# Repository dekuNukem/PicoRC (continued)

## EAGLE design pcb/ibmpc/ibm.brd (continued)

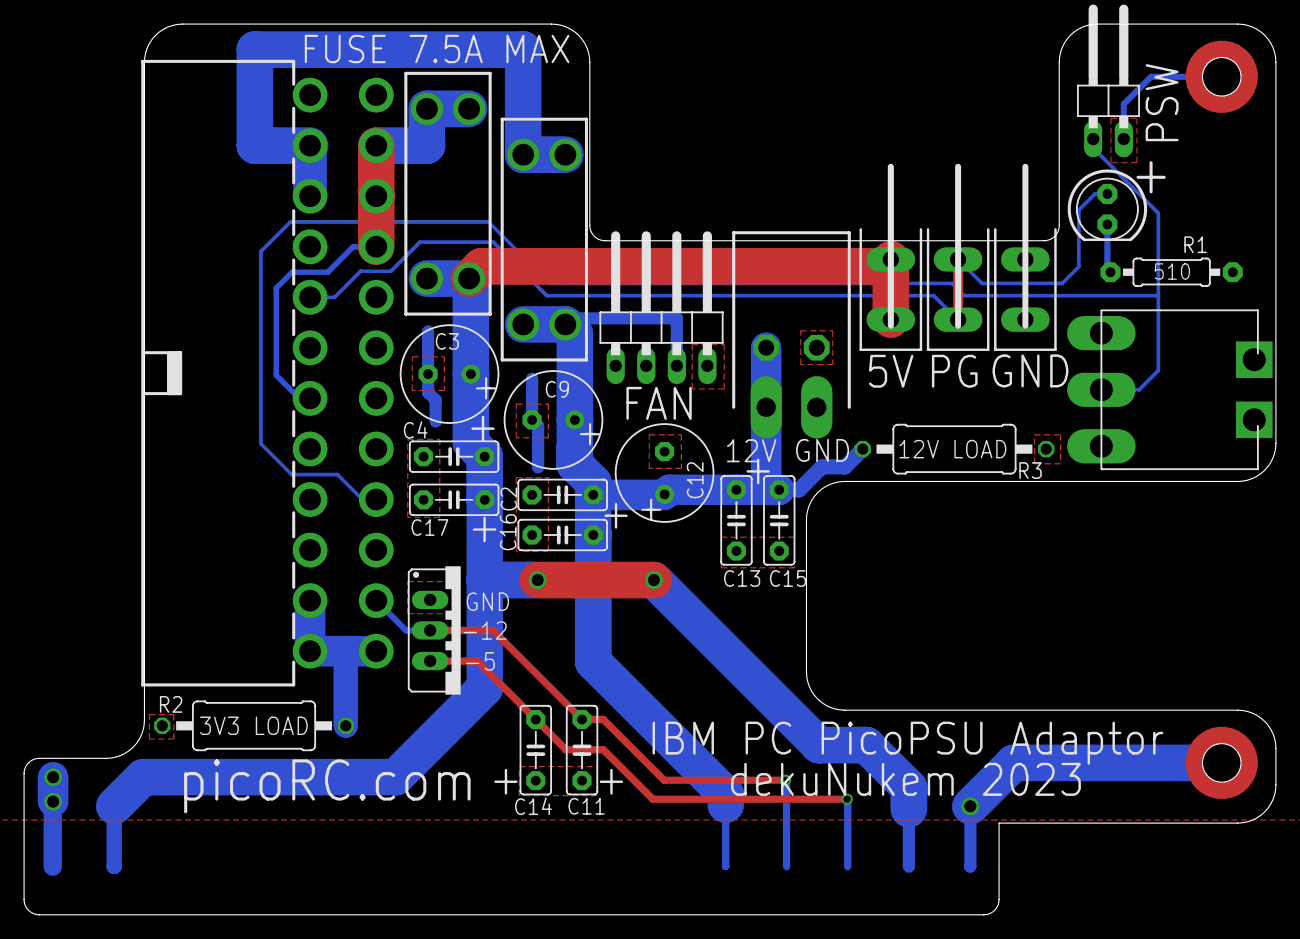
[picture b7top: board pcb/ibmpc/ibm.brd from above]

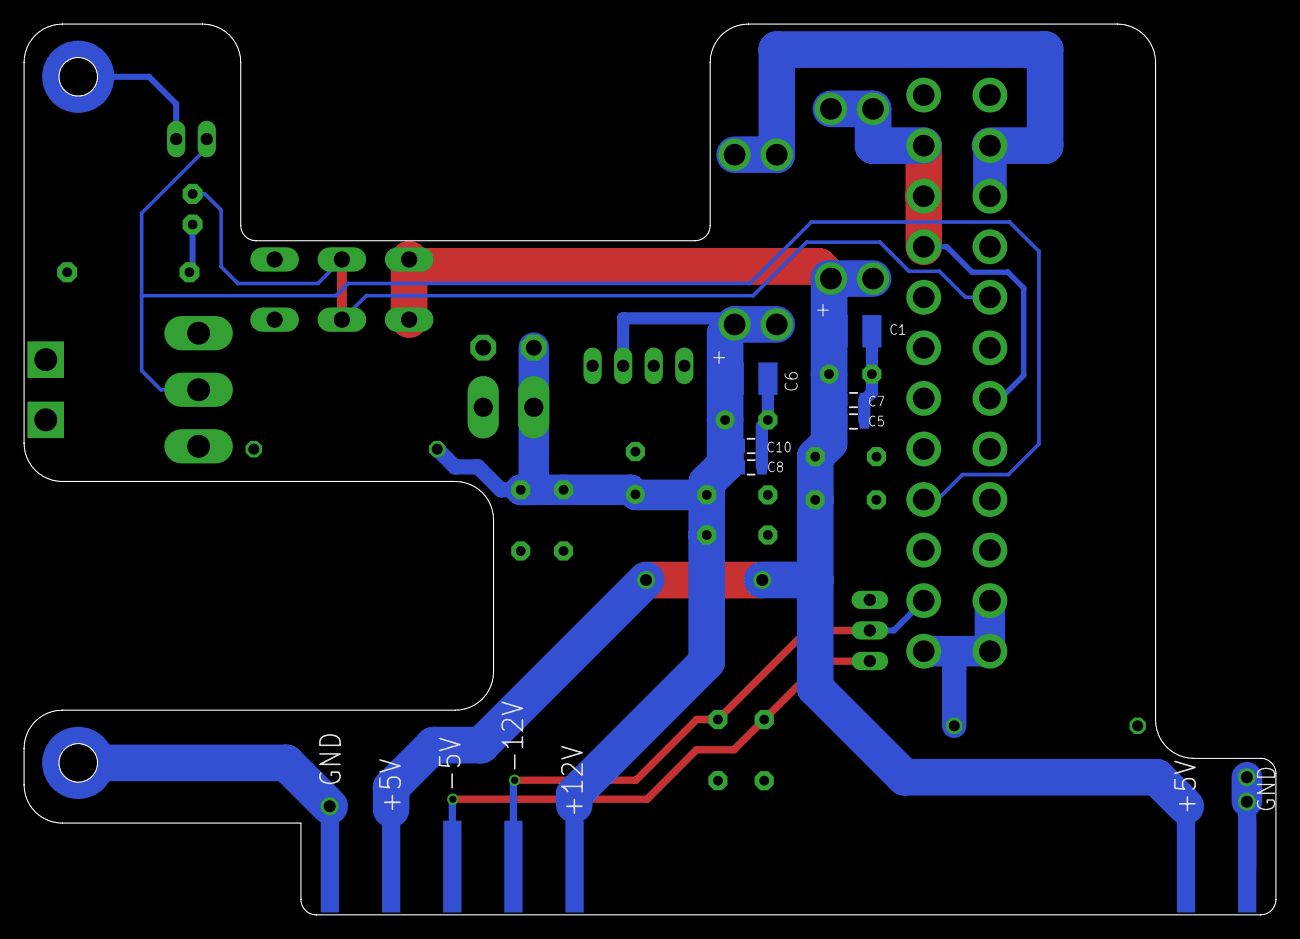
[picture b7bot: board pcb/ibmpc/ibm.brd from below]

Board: 2 copper layers, 104.0 x 74.0 mm, 43 parts (13 on the bottom side), 11 nets.

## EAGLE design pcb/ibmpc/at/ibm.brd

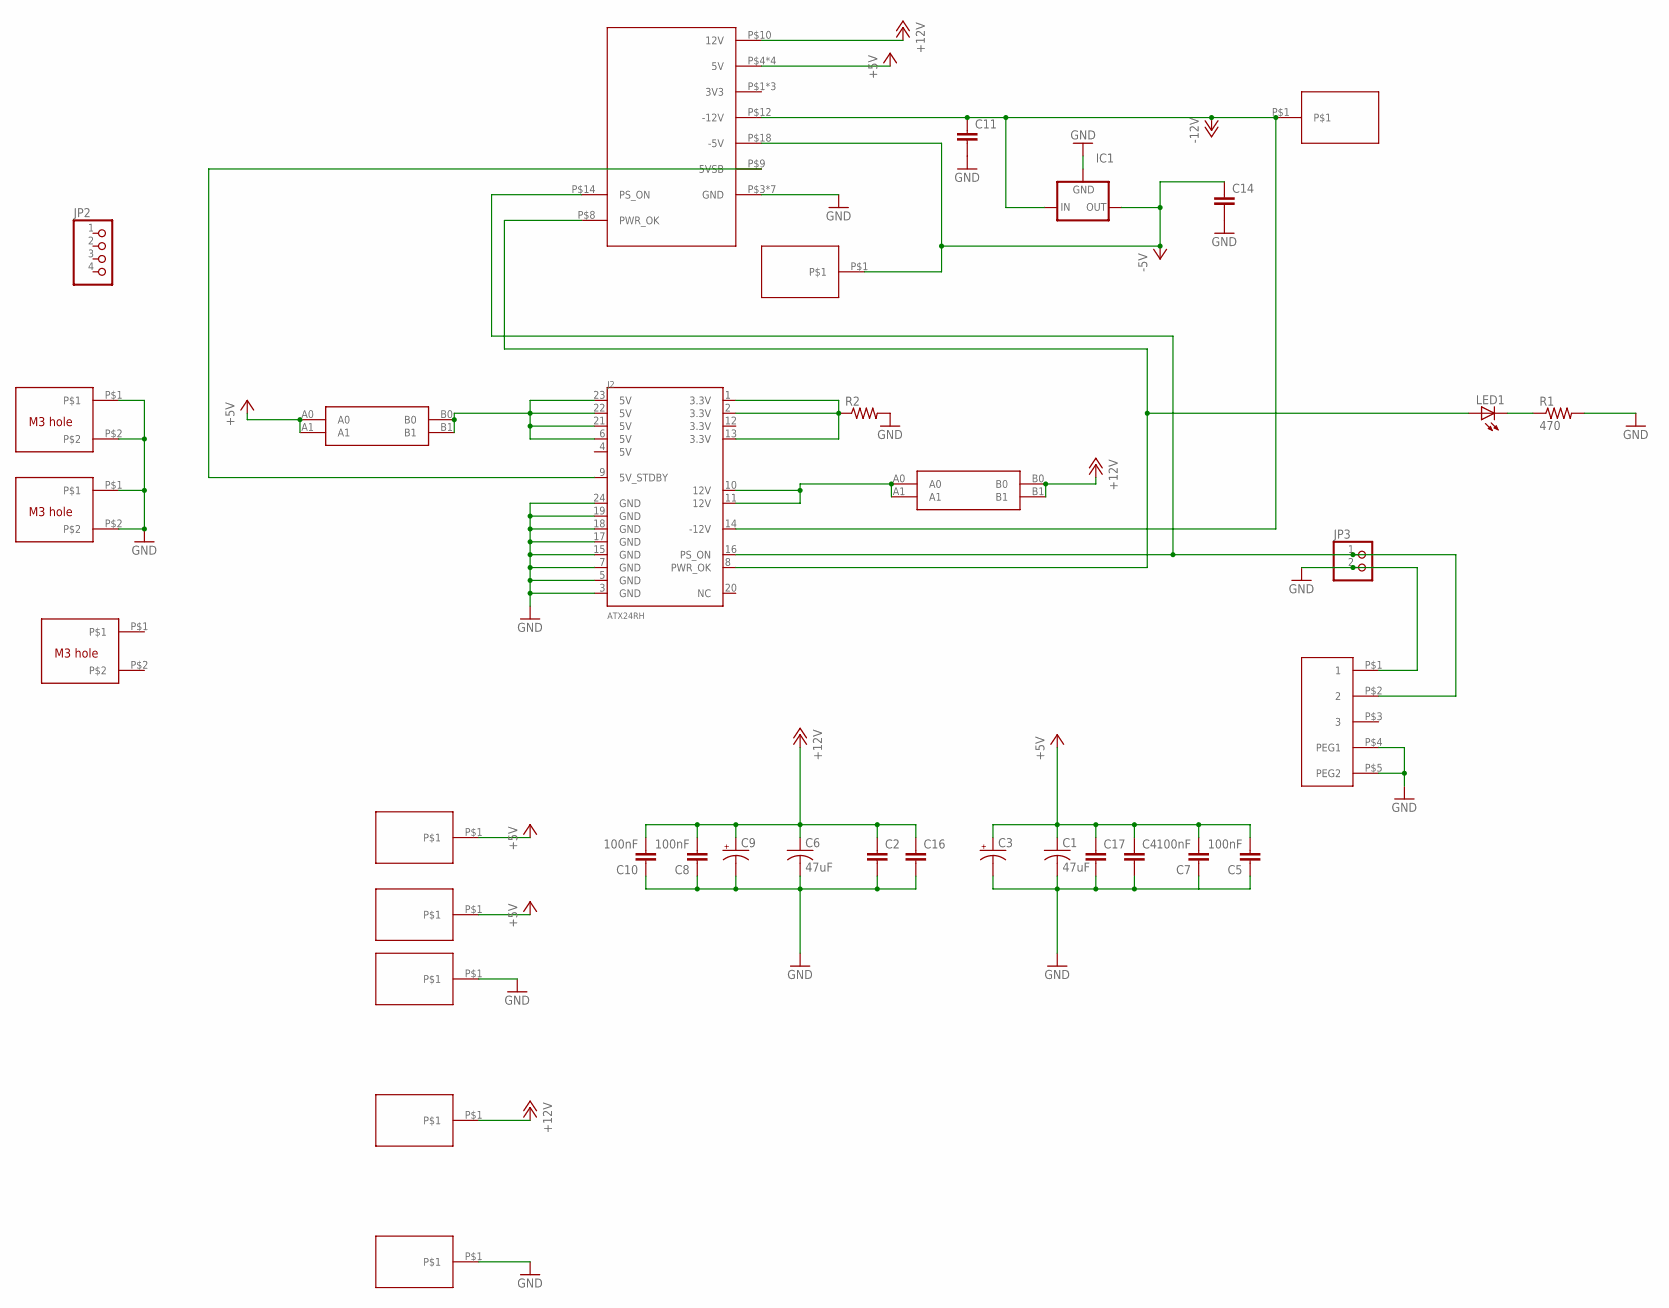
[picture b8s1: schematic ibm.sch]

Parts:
C1, C6: 47uF; C1210
C2, C4, C11, C14, C16, C17: C5/2.5; C5B2.5
C3, C9: CPOL-USE3.5-8; E3,5-8
C5, C7, C8, C10: 100nF; 0805@1
IC1: 79XXS
J2: ATX24RH; ATX24_RIGHT_ANGLE
JP2: PINHD-1X4/90; 1X04/90
JP3: PINHD-1X2/90; 1X02/90
LED1: LED5MM
R1: 470; 0207/10
R2: R-US_0411/15; 0411/15
U$1: 20PEDGE; 20P_EDGE
U$2, U$8: CAR_FUSE_HOLDER3IN1; FUSE_HOLDER_3IN1
U$3, U$7, U$9, U$10, U$13, U$15, U$16: ISA; ISAPAD
U$4: ROCKSW
U$5, U$6, U$11: M3_MOUNTING_HOLE; M3_MOUNTING_HOLE_PACK

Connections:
+5V: C1.1, C3.+, C4.1, C5.2, C7.2, C17.1, U$1.P$4 (5V), U$1.P$6 (5V), U$1.P$19 (5V), U$1.P$20 (5V), U$3.P$1, U$8.A0, U$8.A1, U$16.P$1
+12V: C2.1, C6.1, C8.2, C9.+, C10.2, C16.1, U$1.P$10 (12V), U$2.B0, U$2.B1, U$13.P$1
-5V: C14.1, IC1.OUT, U$1.P$18 (-5V), U$7.P$1
-12V: C11.1, IC1.IN, J2.14 (-12V), U$1.P$12 (-12V), U$10.P$1
GND: C1.2, C2.2, C3.-, C4.2, C5.1, C6.2, C7.1, C8.1, C9.-, C10.1, C11.2, C14.2, C16.2, C17.2, IC1.GND, J2.3 (GND), J2.5 (GND), J2.7 (GND), J2.15 (GND), J2.17 (GND), J2.18 (GND), J2.19 (GND), J2.24 (GND), JP3.2, R1.2, R2.2, U$1.P$3 (GND), U$1.P$5 (GND), U$1.P$7 (GND), U$1.P$13 (GND), U$1.P$15 (GND), U$1.P$16 (GND), U$1.P$17 (GND), U$4.P$1 (1), U$4.P$4 (PEG1), U$4.P$5 (PEG2), U$5.P$1, U$5.P$2, U$6.P$1, U$6.P$2, U$9.P$1, U$15.P$1
unnamed: J2.1 (3.3V), J2.2 (3.3V), J2.13 (3.3V), R2.1
unnamed: J2.16 (PS_ON), JP3.1, U$1.P$14 (PS_ON), U$4.P$2 (2)
unnamed: J2.8 (PWR_OK), LED1.A, U$1.P$8 (PWR_OK)
unnamed: J2.9 (5V_STDBY), U$1.P$9 (5VSB)
unnamed: J2.6 (5V), J2.21 (5V), J2.22 (5V), J2.23 (5V), U$8.B0, U$8.B1
unnamed: J2.10 (12V), J2.11 (12V), U$2.A0, U$2.A1
unnamed: LED1.K (C), R1.1

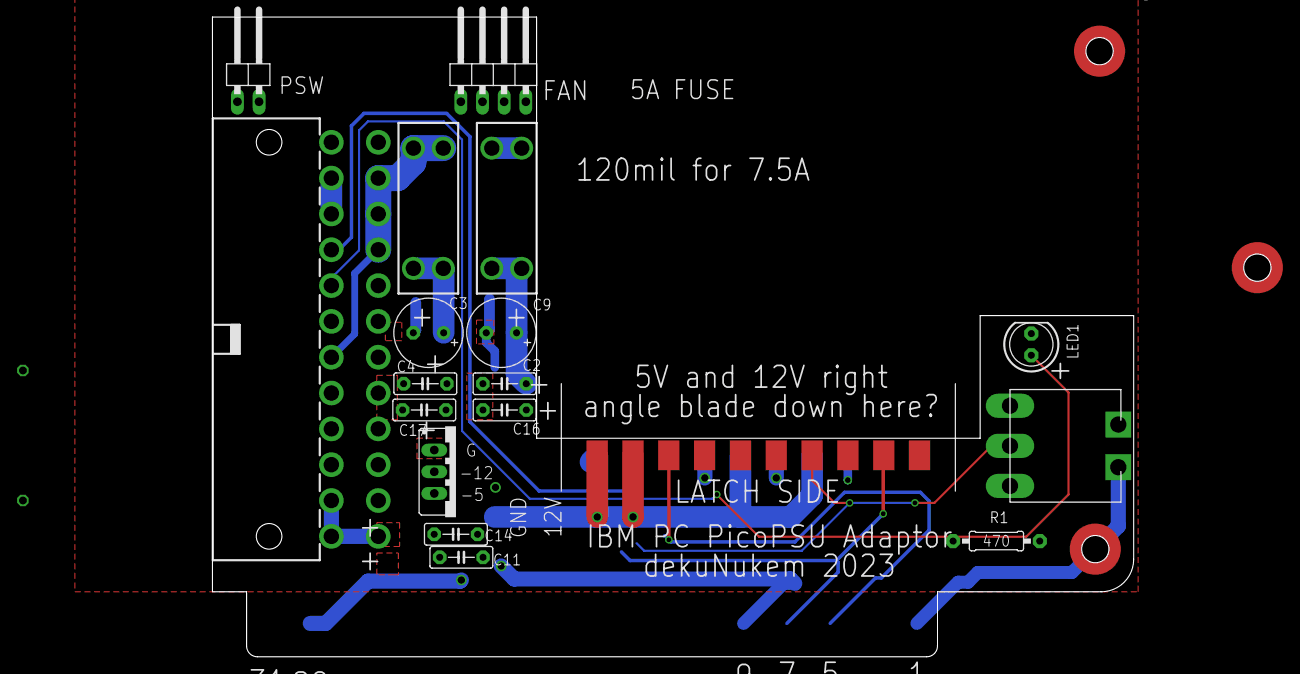
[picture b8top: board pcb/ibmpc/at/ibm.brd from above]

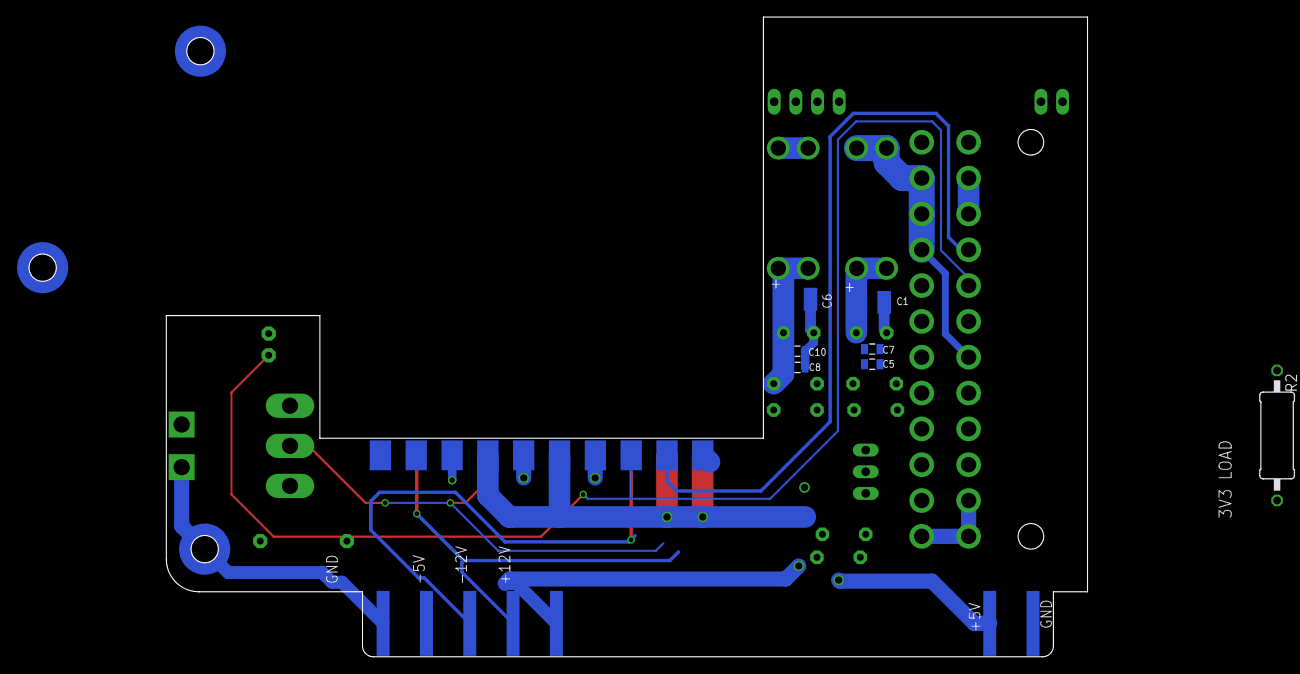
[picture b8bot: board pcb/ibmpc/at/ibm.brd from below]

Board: 2 copper layers, 108.0 x 75.0 mm, 35 parts (14 on the bottom side), 12 nets.

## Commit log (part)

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2022-12-12 moved files from ATX4VC to here
2022-12-12 writing doc
2022-12-12 updated silkscreen
2022-12-13 updated switch location
2022-12-16 updated pcb
2022-12-19 added iigs power header
2022-12-20 added iigs
2023-01-25 added macse
2023-01-25 added apple ii
2023-01-25 cleanup
2023-01-25 updated links
2023-01-25 fixed typo
2023-02-08 added instruction about nylon rivets
2023-03-09 added BBC micro
2023-03-09 added one more -5v rail
2023-03-09 finishing touches
2023-03-27 BBC micro USB adaptor
2023-04-03 added osborne 1
2023-04-05 working on edgeplate
2023-04-08 updated IIGS design
2023-04-08 updated silkscreen and improved GND return
2023-04-08 updated bbc micro PCB
2023-04-09 cleaned up photo link
2023-04-09 changed bbc micro PCB with LM2776
2023-04-09 clean up for production run
2023-04-10 fixed header photo
2023-04-11 fixed a silkscreen error
2023-04-14 added one more power connector, added decoupling cap
2023-04-15 changed oritation
2023-04-15 correct orientation to allow grounding blade
2023-04-15 minor cleanup
2023-04-17 adjusted lm2776 footprint
2023-04-18 updated new photos with PCB blanking plate
2023-04-19 writing doc for IIGS
2023-04-20 added money shot
2023-04-20 new photos
2023-04-20 clean up wording
2023-04-20 updated parts
2023-04-21 working on osborne 1
2023-04-21 adjusted switch position
2023-04-21 added more photos
2023-04-21 fixed broken link
2023-04-24 added product link
2023-04-24 added stl files for mac SE plates
2023-06-01 bbc run
2023-06-09 minor
2023-06-10 added apricot pc
2023-06-10 added more caps
2023-06-10 adjusted holes
2023-06-18 added grounding blade and exposed screw pad, added psw blade
2023-06-19 minor adjustment before production
2023-06-19 working on ibmpc
2023-06-19 ibmpc done
2023-06-19 adjust apricot pc resistors
2023-06-20 changed ibm switch position
2023-06-26 fixed connector oritation
2023-06-27 changed to 70L05
2023-06-27 switched back to 7905
2023-06-27 added ISA legs
2023-06-27 LED now shows power good signal
2023-06-30 minor adjustments
2023-07-03 connected up switch, adjusted mounting hole
2023-07-03 changed to small diameter caps
2023-07-03 changed to smaller diameter caps
2023-07-03 added blanking plate
2023-07-04 cleanup for new run
2023-07-05 adding fingers
2023-07-05 added voltage blaster features, removed 3.3V
2023-07-10 added fingers for 5V and 12V, minor adjustments
2023-07-11 added 3V3 load resistor, flipped board around
2023-07-11 moved psw header location
2023-07-13 working on apricot PC
2023-07-14 adjusted opening
2023-07-17 added apricot PC and BBC micro
2023-07-17 updated new version
2023-07-17 updated apple II doc
2023-07-17 added product links
2023-07-21 working on IBM card
2023-07-22 working on new version
2023-07-22 added more caps to OS1
2023-07-24 cleaned up links
2023-07-24 clean up
2023-07-25 updated fan header
2023-07-27 adjusted USB opening and text
2023-07-28 removed fan voltage selector
2023-07-28 working on improvements
2023-07-31 added 12V load resistor and blade
2023-08-01 updated with more caps
2023-08-04 fixed a typo
2023-08-12 updated OS1 guide with new revision
2023-08-12 working on ibm
2023-08-14 adjusted footprint
2023-08-16 writing
2023-08-16 writing about big red switch
2023-08-17 working on 5155
2023-08-17 5155 write
2023-08-17 more photos
2023-08-19 putting 5155 in its own article
2023-08-22 cleaning up
2023-08-22 added more about big red switch
2023-08-22 added ibm money shot
2023-09-07 updated photos
2023-09-07 updated docs
2023-09-24 updated blanking plate
2023-09-24 trace cleanup
2023-11-07 updated 5155 and PC warning
2023-12-28 updated part list
2023-12-28 updated mac128k guide
2024-01-23 adding guide for early osborne 1
2024-01-23 early osborne 1
2024-03-17 added instruction for eariler apple IIs
2024-03-17 enlarged blanking plate for apple II and II plus
2024-04-04 pcb se30 blanking plate
2024-04-27 added isa bracket
2024-10-28 silkscreen adjustment
2024-10-28 using github pages
2025-03-03 updated backplate
2025-03-13 test fit adjustment
2025-03-22 added osborne1 stl files
2025-03-23 added BBC master instructions
2025-05-26 added gerbers
2025-09-18 rev2, added internal usbc port, silkscreen cleanup
2025-09-18 adjusted jumper angle, fixed pin bug
2025-10-15 working on improved os1 design
2025-10-15 added docs
2025-10-15 working on trs80_m2
2025-10-16 trs80m2 done
2025-10-16 new os1 pcb done
2025-10-25 isolated pe and gnd
2025-10-25 reworking trs80m2
2025-11-22 added 3d models and gerber files
2025-12-04 added 3d print
2026-02-19 adjust pcb
2026-02-19 working on os1
2026-02-20 working on sirius 1
2026-02-20 396 sirius1
2026-02-21 working on mw psu footprint
2026-02-21 sirius 1 done
2026-02-21 file cleanup
2026-02-21 adjust inductor hole size
2026-02-21 mw os1
2026-02-21 adjusted thermals
2026-02-21 adjusted silkscreen
2026-03-04 m3 holes, moved PSU down slighly, thicker 12V trace
2026-03-21 new branch
2026-03-21 working on sirius 1 doc
2026-03-22 doc clean
2026-03-22 more writing
2026-03-23 doc close to done
2026-04-01 doc cleanup
2026-04-01 updated purchase links
2026-04-02 update wording
2026-04-03 enlarged m3 hole slightly
2026-04-07 updated instruction
2026-05-09 updated osborne 1 pcb
2026-05-23 update os1 pcb
2026-05-24 mean well osborne 1
2026-05-24 os1 early meanwell
2026-05-24 fix typo
2026-05-25 adjust wording
2026-05-28 adjust trace spacing
